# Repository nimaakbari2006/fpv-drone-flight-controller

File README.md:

# Custom FPV Drone — Power Distribution Board & Flight Controller

Two custom PCBs designed from scratch in KiCad for a 5-inch FPV drone, plus complete component selection and compatibility validation for the full build. This project covers the full stack: switching power supply design, a Betaflight-compatible flight controller, and systems-level integration of the entire aircraft.

---

## Overview

The goal was to replace the stock electronics of a 5-inch FPV drone with custom-designed hardware, as an electrical engineering portfolio project. Two boards were designed:

1. **Power Distribution Board (PDB)** — takes 4S LiPo battery input and generates regulated 5V and 3.3V rails while distributing raw battery power to the ESC.
2. **Flight Controller (FC)** — an STM32F405-based, Betaflight-compatible flight controller with a full peripheral set.

Both boards were designed to the standard 30.5 × 30.5 mm FPV stack mounting pattern to integrate with the airframe and ESC.

---

## Power Distribution Board

A dual-output switching power supply feeding the drone's electronics.

**Key features:**
- 4S LiPo (up to ~16.8V) input with XT60 connection
- Two synchronous buck converters (MP2307) generating **5V** and **3.3V**
- Input protection: SM6T22A TVS diode against voltage spikes
- Raw battery pass-through (VBATOUT) to the 4-in-1 ESC via wide copper
- Feedback dividers, compensation networks, soft-start, and proper input/output decoupling on each channel

**Design decisions:**
- Chose the **MP2307 synchronous buck** over the older LM2596 after finding that the LM2596's through-hole inductors exceeded the frame's stack-height clearance — a real mechanical constraint that drove the part selection toward a smaller SMD synchronous design.
- Replaced the large through-hole bulk capacitor with an SMD polymer cap to fit the board within the mounting footprint.

*(See `/PDB/` for schematic, layout, 3D render, and Gerbers.)*

---

## Flight Controller

A full-featured, Betaflight-compatible flight controller.

**Core:**
- **STM32F405RGT6** MCU (LQFP-64)
- **ICM-42688-P** gyro/accelerometer over SPI1
- 8 MHz crystal, full power decoupling, VCAP, reset & boot circuitry
- USB-C for configuration and firmware flashing (with CC pulldowns and power-OR Schottky)
- Onboard 3.3V LDO so the board runs from USB alone on the bench

**Peripherals:**
- **AT7456E OSD** for on-screen display over the analog video feed (SPI3)
- **W25Q128 SPI flash** for blackbox flight logging
- 4 motor outputs (DShot-capable timer pins) + ESC telemetry & current sense
- ELRS receiver UART, VTX (SmartAudio) control, GPS UART
- Analog camera input and VTX video output through the OSD
- Battery voltage sensing, buzzer driver, addressable LED output
- SWD debug header

**Design decisions:**
- Followed the official **Betaflight F405 pin mapping** so the board matches an existing firmware target rather than requiring a custom one (gyro on SPI1, OSD/flash sharing SPI3, careful UART assignment to avoid the DFU/USART conflict).
- **4-layer stackup** with a dedicated internal ground plane beneath the IMU for clean gyro readings, and controlled routing of the USB differential pair.

*(See `/FlightController/` for schematic, layout, 3D render, and Gerbers.)*

---

## Circuit Design & Component Selection

The design methodology was datasheet-driven: each IC's manufacturer datasheet specifies a recommended application circuit, and following those recommended values — for decoupling, compensation, loop stability, and support components — is the correct engineering practice rather than guessing or reinventing them. Where the design required application-specific values that the datasheet does not give directly (chiefly the regulator output voltages and the battery-sense scaling), those were calculated from the relevant equations. This section documents both.

### Values sourced from datasheets and reference circuits

The majority of passive values came directly from the manufacturers' recommended application circuits:

- **MCU decoupling** — the STM32F405 datasheet specifies a **100 nF** ceramic at each VDD pin plus a shared bulk capacitor; the **2.2 µF** low-ESR capacitors on the VCAP core-regulator pins are a hard datasheet requirement (the internal core regulator will not start without them).
- **Analog supply filtering** — the **600 Ω @ 100 MHz** ferrite bead plus **1 µF / 100 nF** VDDA filter follows ST's recommended arrangement to keep digital switching noise off the ADC reference.
- **Buck converter support** — the MP2307's loop-compensation R–C network, **10 nF** soft-start capacitor, **10 nF** bootstrap capacitor, and input/output capacitor values were taken from the MP2307 datasheet's typical application circuit for the chosen inductor and output-cap combination.
- **IMU** — the ICM-42688-P's supply decoupling (**2.2 µF + 100 nF**) follows TDK's reference circuit, and its reserved pins were terminated exactly as the datasheet pin-description table specifies.
- **OSD** — the on-screen-display support components and crystal frequency were taken from the OSD device's datasheet and a known-good reference design.

Using the datasheet's recommended circuit is deliberate: manufacturers characterise these values for stability and noise performance, and deviating from them without reason is how power supplies end up oscillating or ICs end up unstable.

### Values calculated for this design

A few values are application-specific and were derived rather than copied:

**Buck converter output voltages (feedback dividers).** The MP2307 servos its feedback pin to an internal 0.925 V reference; the output is set by a divider:

```
Vout = 0.925 V × (1 + Rtop / Rbot)
```

With Rbot fixed at 10 kΩ, Rtop was solved for each rail:
- **5V rail:** Rtop ≈ 44.05 kΩ → nearest E96 value **44.2 kΩ** (gives 5.01 V)
- **3.3V rail:** Rtop ≈ 25.68 kΩ → nearest E96 value **25.5 kΩ** (gives 3.28 V)

1% (E96) resistors were used so output accuracy is set by the reference and divider, not resistor drift.

**Battery voltage sensing.** A **100 kΩ / 10 kΩ** divider scales the raw battery voltage down to the STM32's 3.3 V ADC range: at 4S full charge (16.8 V) the ADC sees ~1.5 V, at 6S (25.2 V) ~2.3 V — both safely under the 3.3 V limit with headroom. This matches Betaflight's default voltage-sensing scale.

**Crystal load capacitors.** Sized from the crystal's specified load capacitance and estimated board stray capacitance using `Cload_cap ≈ 2 × (CL − Cstray)`, giving **~22 pF** per oscillator node.

### Values set by standards

- **5.1 kΩ** pull-downs on the USB-C CC pins — the specific value required by the USB-C specification for a device to advertise itself and draw bus power.
- **75 Ω** termination on the analog video lines — matches the standard 75 Ω video signal impedance.

### Values from standard digital-design practice

Pull-ups and pull-downs were chosen high enough to draw negligible current but low enough to hold a defined logic level against pin leakage — **10 kΩ** for the NRST pull-up, BOOT0/BOOT1 pull-downs, and the SPI flash/OSD chip-select and hold lines; **100 kΩ** for the buzzer MOSFET gate pull-down so it stays off while its GPIO is floating during boot.

---

## Full Drone Build & Component Selection

Beyond the PCBs, the project involved specifying and validating an entire FPV drone, ensuring every component is electrically and mechanically compatible.

**Key selection decisions:**
- **Motors:** iFlight XING 2207 **1800KV** — the correct kV range for a 4S 5-inch freestyle build (higher-kV variants are 2–4S racing parts).
- **Video system:** a fully **analog 5.8GHz** chain — RunCam Robin 3 → JHEMCU VTX20-600 → FlyFishRC Osprey antenna → goggles — with **RHCP** polarization matched from drone to goggles.
- **Control link:** **ELRS 2.4GHz** (RadioMaster Pocket + Nano RX), both on FCC firmware for region compatibility.
- **ESC:** 55A rating, sized comfortably above the motors' ~35A peak draw.

**Interface & connector compatibility** (each verified against the actual component pinouts):
- FC ↔ ESC: 8-pin JST-SH (motor signals, telemetry, current, power)
- FC ↔ Camera: 6-pin JST-SH, wired to the RunCam Robin 3's pinout (power, GND, video, camera control)
- FC ↔ VTX: 4-pin (video, GND, battery, SmartAudio)
- FC ↔ GPS / Receiver: JST-SH UART connectors
- Video RF: MMCX (VTX to antenna), RHCP polarization matched throughout

*(See `/BOM/FPV_Drone_BOM.xlsx` for the complete bill of materials with compatibility notes.)*

---

## Tools & Skills

**KiCad** · schematic capture · PCB layout · 4-layer stackup design · switching power supply design · SPI/UART bus architecture · USB routing · DRC/ERC verification · library management (symbol/footprint import) · datasheet-driven design · systems integration · component selection & compatibility analysis

---

## Status

Both boards are fully designed and verified in KiCad (ERC and DRC clean). Manufacturing files (Gerbers, BOM, placement) generated for fabrication and assembly. Full drone build specified and components sourced.

*Physical assembly and flight testing to follow — this README will be updated with assembly photos and results.*

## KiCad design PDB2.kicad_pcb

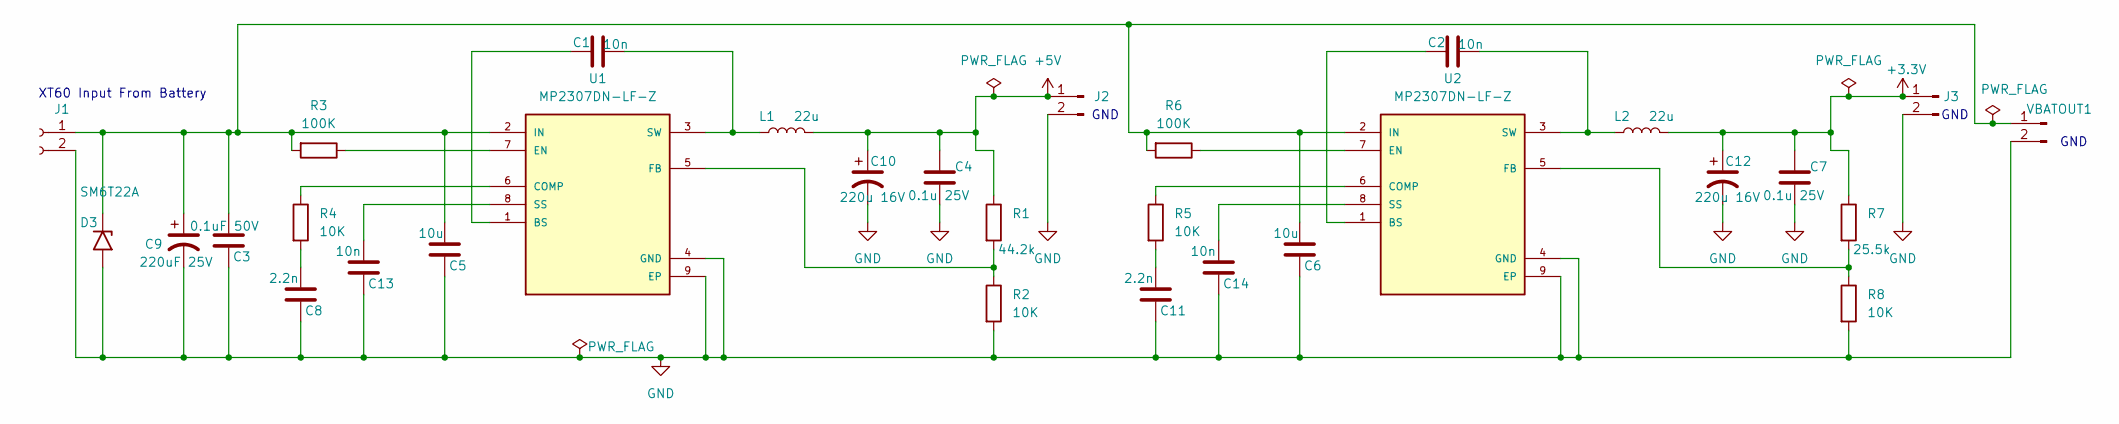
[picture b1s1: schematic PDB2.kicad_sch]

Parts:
C1, C2, C13, C14: 10n; C_0805_2012Metric_Pad1.18x1.45mm_HandSolder
C3: 0.1uF 50V; C_0805_2012Metric_Pad1.18x1.45mm_HandSolder
C4, C7: 0.1u 25V; C_0805_2012Metric_Pad1.18x1.45mm_HandSolder
C5, C6: 10u; C_0805_2012Metric_Pad1.18x1.45mm_HandSolder
C8, C11: 2.2n; C_0805_2012Metric_Pad1.18x1.45mm_HandSolder
C9: 220uF 25V; CP_Elec_8x10.5
C10, C12: 220u 16V; CP_Radial_D8.0mm_P3.50mm
D3: SM6T22A; D_SMB
J1: Conn_01x02_Socket; SolderWire-4sqmm_1x02_P12mm_D3mm_OD6mm
J2, J3: Conn_01x02_Pin; PinHeader_1x02_P2.54mm_Vertical
L1, L2: 22u; L_TDK_SLF7045
R1: 44.2k; R_0805_2012Metric_Pad1.20x1.40mm_HandSolder
R2, R4, R5, R8: 10K; R_0805_2012Metric_Pad1.20x1.40mm_HandSolder
R3, R6: 100K; R_0805_2012Metric_Pad1.20x1.40mm_HandSolder
R7: 25.5k; R_0805_2012Metric_Pad1.20x1.40mm_HandSolder
U1, U2: MP2307DN-LF-Z; SOIC127P600X170-9N; PARTREV 1.9; DigiKey_Part_Number 1589-1576-1-ND
VBATOUT1: Conn_01x02_Pin; SolderWire-4sqmm_1x02_P12mm_D3mm_OD6mm

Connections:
+3.3V: C7.1, C12.1, J3.1, L2.2, R7.1
+5V: C4.1, C10.1, J2.1, L1.2, R1.1
GND: C3.2, C4.2, C5.2, C6.2, C7.2, C8.2, C9.2, C10.2, C11.2, C12.2, C13.2, C14.2, D3.2 (A2), J1.2, J2.2, J3.2, R2.2, R8.2, U1.4 (GND), U1.9 (EP), U2.4 (GND), U2.9 (EP), VBATOUT1.2
unnamed: C8.1, R4.2
unnamed: C11.1, R5.2
unnamed: C3.1, C5.1, C6.1, C9.1, D3.1 (A1), J1.1, R3.2, R6.2, U1.2 (IN), U2.2 (IN), VBATOUT1.1
unnamed: C1.2, U1.1 (BS)
unnamed: R4.1, U1.6 (COMP)
unnamed: R3.1, U1.7 (EN)
unnamed: R1.2, R2.1, U1.5 (FB)
unnamed: C13.1, U1.8 (SS)
unnamed: C1.1, L1.1, U1.3 (SW)
unnamed: C2.2, U2.1 (BS)
unnamed: R5.1, U2.6 (COMP)
unnamed: R6.1, U2.7 (EN)
unnamed: R7.2, R8.1, U2.5 (FB)
unnamed: C14.1, U2.8 (SS)
unnamed: C2.1, L2.1, U2.3 (SW)

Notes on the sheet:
XT60 Input From Battery
GND

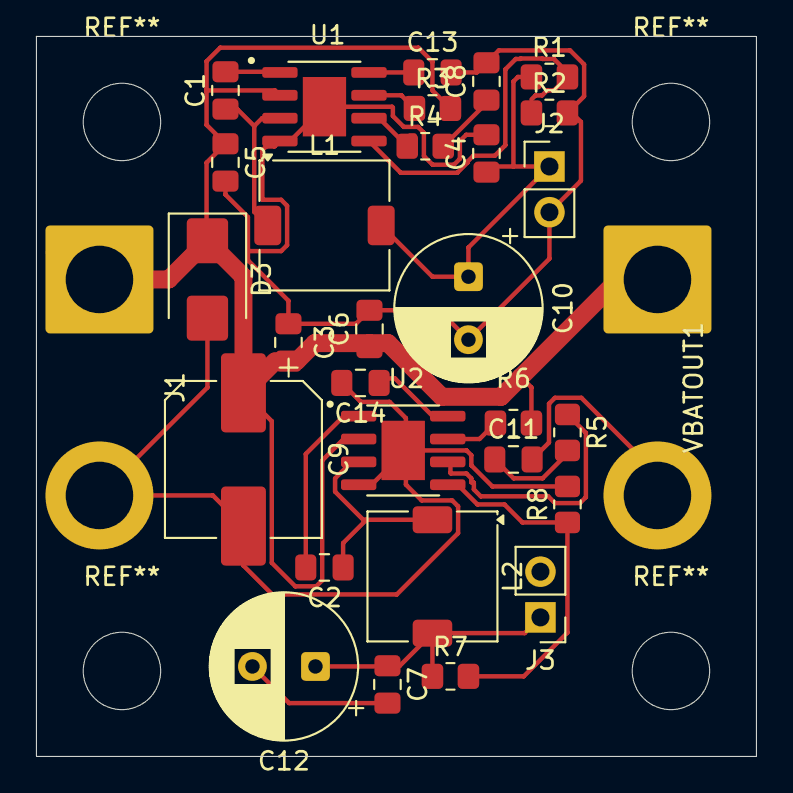
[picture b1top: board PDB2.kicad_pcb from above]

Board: 2 copper layers, 40.0 x 40.0 mm, 31 parts (0 on the bottom side), 18 nets.

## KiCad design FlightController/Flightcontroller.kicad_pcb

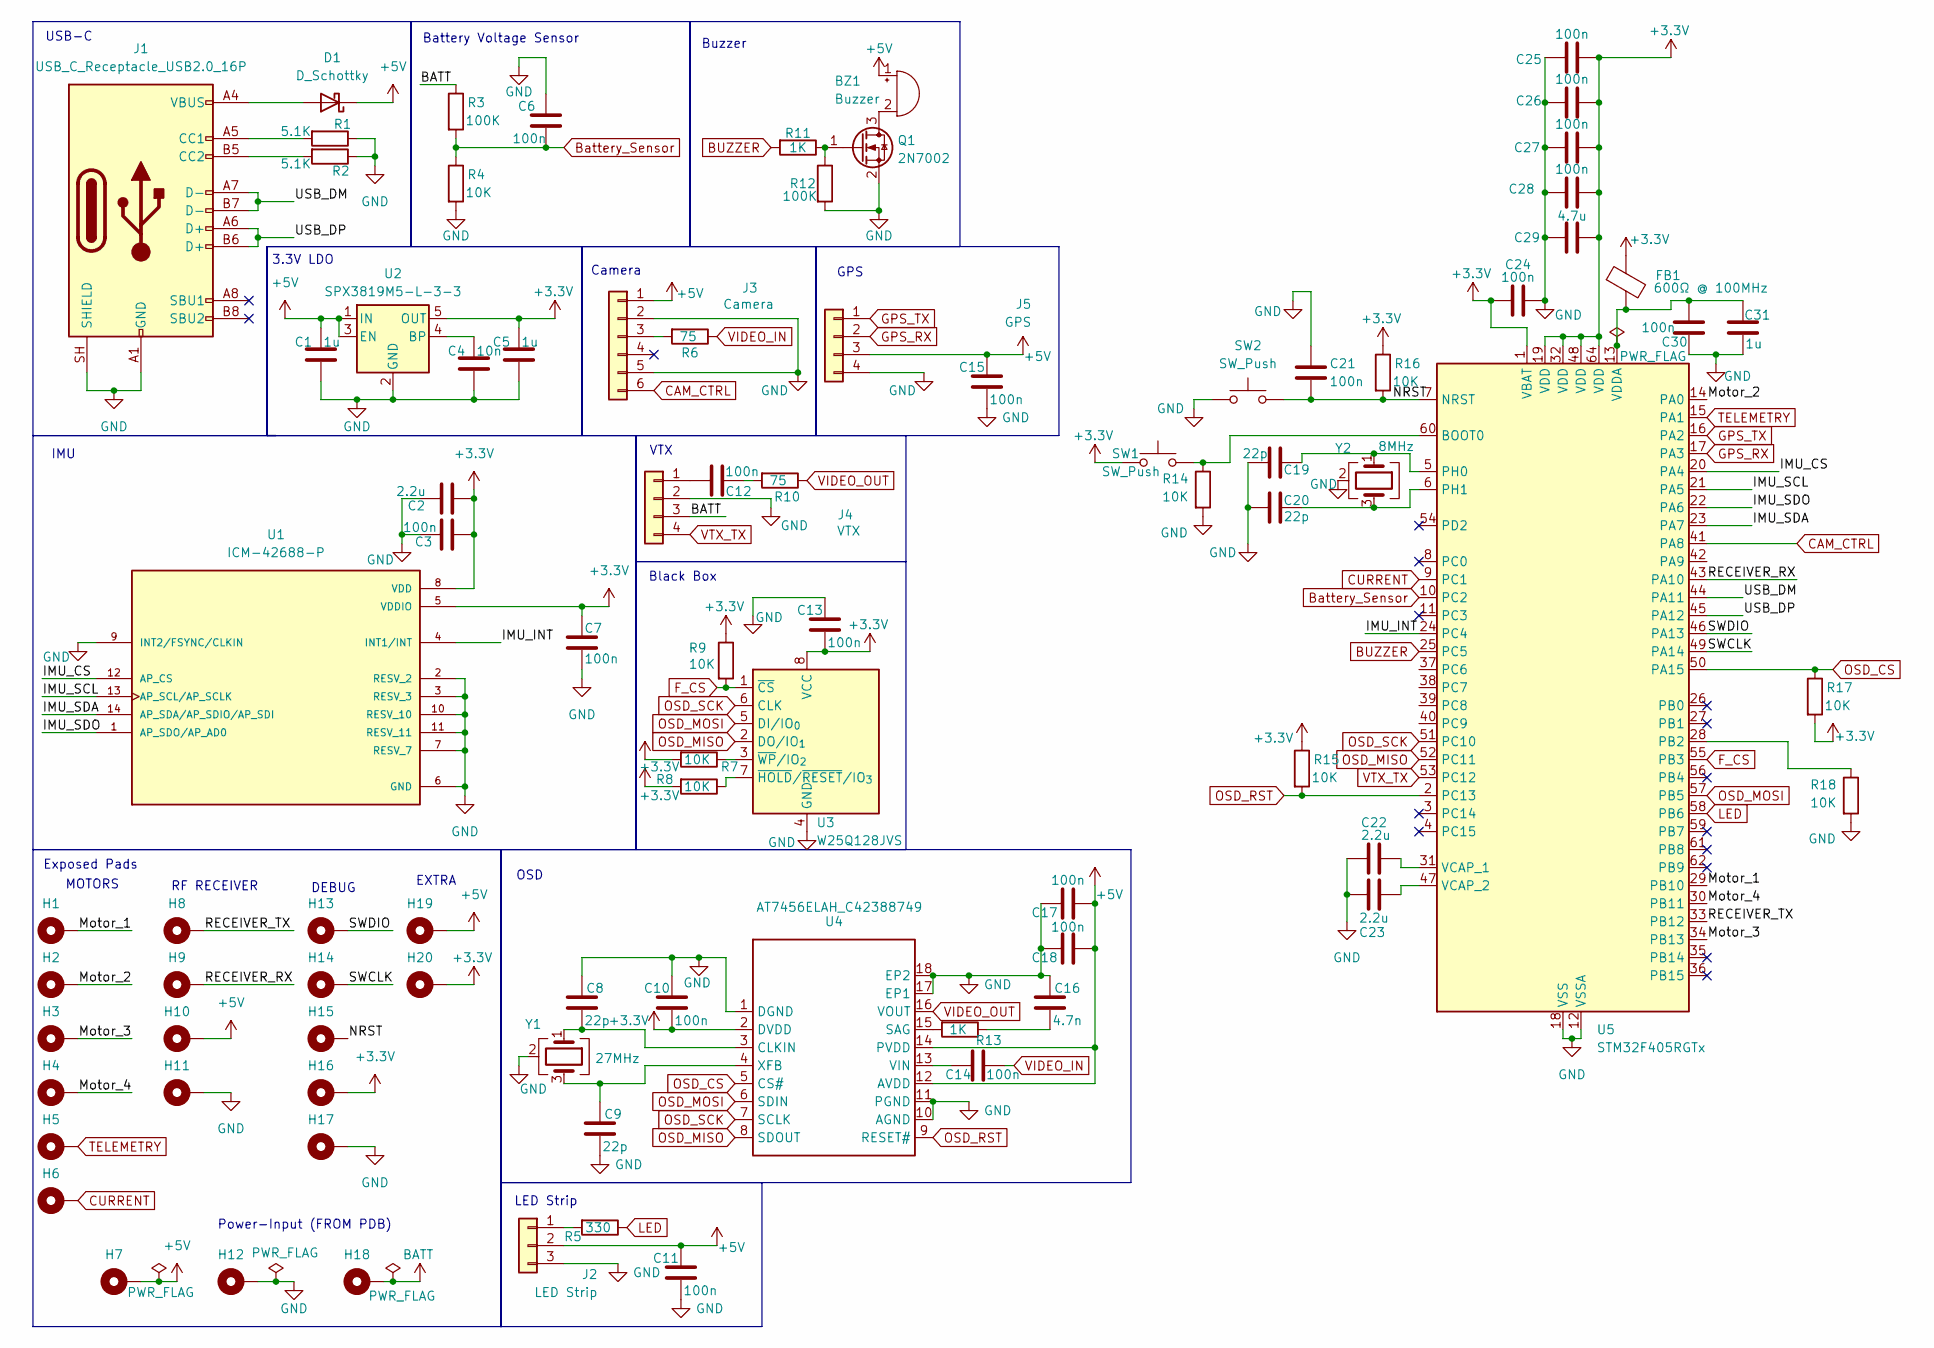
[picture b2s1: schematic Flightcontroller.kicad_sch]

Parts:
BZ1: Buzzer; Buzzer_CUI_CPT-9019S-SMT
C1, C5, C31: 1u; C_0805_2012Metric_Pad1.18x1.45mm_HandSolder
C2, C22, C23: 2.2u; C_0805_2012Metric_Pad1.18x1.45mm_HandSolder
C3, C6, C7, C10, C11, C12, C13, C14, C15, C17, C18, C21, C24, C25, C26, C27, C28, C30: 100n; C_0805_2012Metric_Pad1.18x1.45mm_HandSolder
C4: 10n; C_0805_2012Metric_Pad1.18x1.45mm_HandSolder
C8, C9, C19, C20: 22p; C_0805_2012Metric_Pad1.18x1.45mm_HandSolder
C16: 4.7n; C_0805_2012Metric_Pad1.18x1.45mm_HandSolder
C29: 4.7u; C_0805_2012Metric_Pad1.18x1.45mm_HandSolder
D1: D_Schottky; D_SOD-123
FB1: 600Ω @ 100MHz; L_0805_2012Metric_Pad1.05x1.20mm_HandSolder
H1: Motor_1; TestPoint_Pad_D1.5mm
H2: Motor_2; TestPoint_Pad_D1.5mm
H3: Motor_3; TestPoint_Pad_D1.5mm
H4: Motor_4; TestPoint_Pad_D1.5mm
H5: TELEMETRY; TestPoint_Pad_D1.5mm
H6: CURRENT; TestPoint_Pad_D1.5mm
H7: 5V; TestPoint_Pad_D2.5mm
H8: RECEIVER_TX; TestPoint_Pad_D1.5mm
H9: RECEIVER_RX; TestPoint_Pad_D1.5mm
H10: 5V; TestPoint_Pad_D1.5mm
H11: GND; TestPoint_Pad_D1.5mm
H12: GND; TestPoint_Pad_D2.5mm
H13: SWDIO; TestPoint_Pad_D1.0mm
H14: SWCLK; TestPoint_Pad_D1.0mm
H15: NRST; TestPoint_THTPad_D2.0mm_Drill1.0mm
H16: 3.3V; TestPoint_Pad_D1.0mm
H17: GND; TestPoint_THTPad_D2.0mm_Drill1.0mm
H18: BATT; TestPoint_Pad_D2.5mm
H19: 5V; TestPoint_THTPad_D2.0mm_Drill1.0mm
H20: 3.3V; TestPoint_THTPad_D2.0mm_Drill1.0mm
J1: USB_C_Receptacle_USB2.0_16P; USB_C_Receptacle_HRO_TYPE-C-31-M-12
J2: LED Strip; JST_SH_SM03B-SRSS-TB_1x03-1MP_P1.00mm_Horizontal
J3: Camera; JST_SH_SM06B-SRSS-TB_1x06-1MP_P1.00mm_Horizontal
J4: VTX; JST_SH_SM04B-SRSS-TB_1x04-1MP_P1.00mm_Horizontal
J5: GPS; JST_SH_SM04B-SRSS-TB_1x04-1MP_P1.00mm_Horizontal
Q1: 2N7002; SOT-23
R1, R2: 5.1K; R_0805_2012Metric_Pad1.20x1.40mm_HandSolder
R3, R12: 100K; R_0805_2012Metric_Pad1.20x1.40mm_HandSolder
R4, R7, R8, R9, R14, R15, R16, R17, R18: 10K; R_0805_2012Metric_Pad1.20x1.40mm_HandSolder
R5: 330; R_0805_2012Metric_Pad1.20x1.40mm_HandSolder
R6, R10: 75; R_0805_2012Metric_Pad1.20x1.40mm_HandSolder
R11, R13: 1K; R_0805_2012Metric_Pad1.20x1.40mm_HandSolder
SW1, SW2: SW_Push; SW_SPST_TL3305A
U1: ICM-42688-P; PQFN50P300X250X97-14N; PARTREV 1.2
U2: SPX3819M5-L-3-3; SOT-23-5
U3: W25Q128JVS; SOIC-8_5.3x5.3mm_P1.27mm
U4: AT7456ELAH_C42388749; LGA-16_L6.8-W4.0-P0.65-TL-2EP
U5: STM32F405RGTx; LQFP-64_10x10mm_P0.5mm
Y1: 27MHz; Crystal_SMD_3225-4Pin_3.2x2.5mm_HandSoldering
Y2: 8MHz; Crystal_SMD_3225-4Pin_3.2x2.5mm_HandSoldering

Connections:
+3.3V: C2.1, C3.1, C5.1, C7.1, C10.2, C13.2, C24.2, C25.1, C26.1, C27.1, C28.1, C29.1, FB1.1, H16.1 (1_1), H20.1, R7.2, R8.2, R9.1, R15.1, R16.1, R17.2, SW1.1, U1.5 (VDDIO), U1.8 (VDD), U2.5 (OUT), U3.8 (VCC), U4.2 (DVDD), U5.1 (VBAT), U5.19 (VDD), U5.32 (VDD), U5.48 (VDD), U5.64 (VDD)
+5V: BZ1.1 (+), C1.1, C11.1, C15.1, C17.1, C18.1, D1.1 (K), H7.1 (1_1), H10.1 (1_1), H19.1, J2.2, J3.1, J5.3, U2.1 (IN), U2.3 (EN), U4.12 (AVDD), U4.14 (PVDD)
/IMU_CS: U1.12 (AP_CS), U5.20 (PA4)
/IMU_INT: U1.4 (INT1/INT), U5.24 (PC4)
/IMU_SCL: U1.13 (AP_SCL/AP_SCLK), U5.21 (PA5)
/IMU_SDA: U1.14 (AP_SDA/AP_SDIO/AP_SDI), U5.23 (PA7)
/IMU_SDO: U1.1 (AP_SDO/AP_AD0), U5.22 (PA6)
/Motor_1: H1.1 (1_1), U5.29 (PB10)
/Motor_2: H2.1 (1_1), U5.14 (PA0)
/Motor_3: H3.1 (1_1), U5.34 (PB13)
/Motor_4: H4.1 (1_1), U5.30 (PB11)
/NRST: C21.2, H15.1, R16.2, SW2.2, U5.7 (NRST)
/RECEIVER_RX: H9.1 (1_1), U5.43 (PA10)
/RECEIVER_TX: H8.1 (1_1), U5.33 (PB12)
/SWCLK: H14.1 (1_1), U5.49 (PA14)
/SWDIO: H13.1 (1_1), U5.46 (PA13)
/USB_DM: J1.A7 (D-), J1.B7 (D-), U5.44 (PA11)
/USB_DP: J1.A6 (D+), J1.B6 (D+), U5.45 (PA12)
BATT: H18.1 (1_1), J4.3, R3.1
BUZZER: R11.2, U5.25 (PC5)
Battery_Sensor: C6.2, R3.2, R4.1, U5.10 (PC2)
CAM_CTRL: J3.6, U5.41 (PA8)
CURRENT: H6.1 (1_1), U5.9 (PC1)
F_CS: R9.2, U3.1 (~CS), U5.55 (PB3)
GND: C1.2, C2.2, C3.2, C4.2, C5.2, C6.1, C7.2, C8.1, C9.2, C10.1, C11.2, C13.1, C15.2, C16.1, C17.2, C18.2, C19.2, C20.2, C21.1, C22.2, C23.2, C24.1, C25.2, C26.2, C27.2, C28.2, C29.2, C30.1, C31.1, H11.1 (1_1), H12.1 (1_1), H17.1, J1.A1 (GND), J1.A12 (GND), J1.B1 (GND), J1.B12 (GND), J1.SH (SHIELD), J2.3, J3.2, J3.5, J4.2, J5.4, Q1.2 (S), R1.1, R2.1, R4.2, R12.2, R14.2, R18.2, SW2.1, U1.2 (RESV_2), U1.3 (RESV_3), U1.6 (GND), U1.7 (RESV_7), U1.9 (INT2/FSYNC/CLKIN), U1.10 (RESV_10), U1.11 (RESV_11), U2.2 (GND), U3.4 (GND), U4.1 (DGND), U4.10 (AGND), U4.11 (PGND), U4.17 (EP1), U4.18 (EP2), U5.12 (VSSA), U5.18 (VSS), U5.63 (VSS), Y1.2 (G), Y1.4 (G), Y2.2 (G), Y2.4 (G)
GPS_RX: J5.2, U5.17 (PA3)
GPS_TX: J5.1, U5.16 (PA2)
LED: R5.1, U5.58 (PB6)
unnamed: BZ1.2 (-), Q1.3 (D)
unnamed: C12.1, R10.2
unnamed: C16.2, R13.1
unnamed: D1.2 (A), J1.A4 (VBUS), J1.A9 (VBUS), J1.B4 (VBUS), J1.B9 (VBUS)
unnamed: J1.A5 (CC1), R1.2
unnamed: J1.B5 (CC2), R2.2
unnamed: J2.1, R5.2
unnamed: J3.3, R6.2
unnamed: C12.2, J4.1
unnamed: Q1.1 (G), R11.1, R12.1
unnamed: C4.1, U2.4 (BP)
unnamed: R8.1, U3.7 (~HOLD/~RESET/IO_{3})
unnamed: R7.1, U3.3 (~WP/IO_{2})
unnamed: C8.2, U4.3 (CLKIN), Y1.1
unnamed: R13.2, U4.15 (SAG)
unnamed: C14.2, U4.13 (VIN)
unnamed: C9.1, U4.4 (XFB), Y1.3
unnamed: R14.1, SW1.2, U5.60 (BOOT0)
unnamed: R18.1, U5.28 (PB2)
unnamed: C19.1, U5.5 (PH0), Y2.1
unnamed: C20.1, U5.6 (PH1), Y2.3
unnamed: C22.1, U5.31 (VCAP_1)
unnamed: C23.1, U5.47 (VCAP_2)
unnamed: C30.2, C31.2, FB1.2, U5.13 (VDDA)
OSD_CS: R17.1, U4.5 (CS#), U5.50 (PA15)
OSD_MISO: U3.2 (DO/IO_{1}), U4.8 (SDOUT), U5.52 (PC11)
OSD_MOSI: U3.5 (DI/IO_{0}), U4.6 (SDIN), U5.57 (PB5)
OSD_RST: R15.2, U4.9 (RESET#), U5.2 (PC13)
OSD_SCK: U3.6 (CLK), U4.7 (SCLK), U5.51 (PC10)
TELEMETRY: H5.1 (1_1), U5.15 (PA1)
VIDEO_IN: C14.1, R6.1
VIDEO_OUT: R10.1, U4.16 (VOUT)
VTX_TX: J4.4, U5.53 (PC12)

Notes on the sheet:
MOTORS
IMU
RF RECEIVER
VTX
Battery Voltage Sensor
Buzzer
Power-Input (FROM PDB)
LED Strip
3.3V LDO
Black Box
USB-C
DEBUG
Exposed Pads
EXTRA
GPS
Camera
OSD

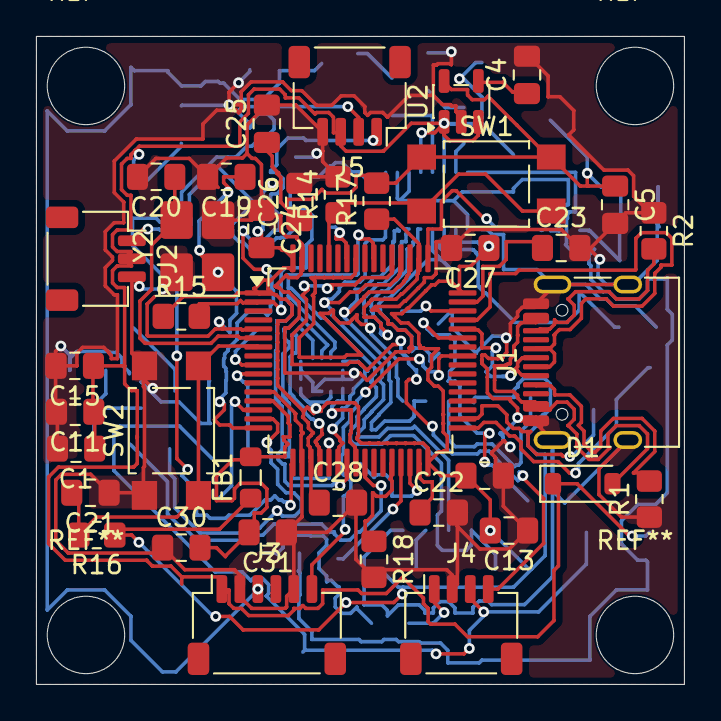
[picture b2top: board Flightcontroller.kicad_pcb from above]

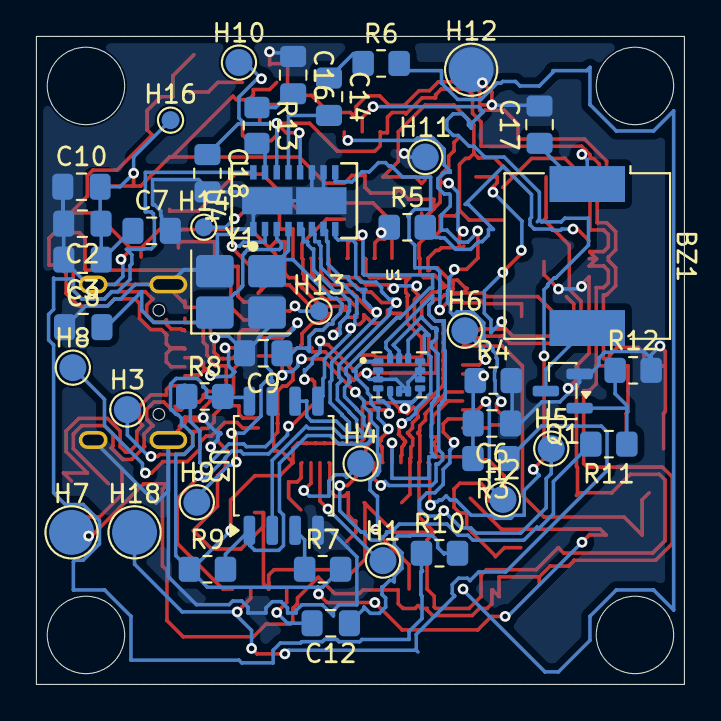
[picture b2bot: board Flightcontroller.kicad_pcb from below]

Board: 4 copper layers, 36.0 x 36.0 mm, 83 parts (45 on the bottom side), 61 nets.
